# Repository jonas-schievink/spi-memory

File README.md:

# `spi-memory`

This crate provides a generic [`embedded-hal`]-based driver for different
families of SPI Flash and EEPROM chips.

Right now, only 25-series Flash chips are supported. Feel free to send PRs to
support other families though!

Please refer to the [changelog](CHANGELOG.md) to see what changed in the last
releases.

[`embedded-hal`]: https://github.com/rust-embedded/embedded-hal

## Usage

Add an entry to your `Cargo.toml`:

```toml
[dependencies]
spi-memory = "0.2.0"
```

Check the [API Documentation](https://docs.rs/spi-memory/) for how to use the
crate's functionality.

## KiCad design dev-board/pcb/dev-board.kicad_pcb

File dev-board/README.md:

# Development / Testing Board

This directory contains design files and software for a development and testing
PCB that can hold up to 16 SPI memory chips using the 25-series pinout.

The PCB features a micro USB receptacle connected to a USB-to-SPI converter, and
can also be mounted on a Raspberry Pi, directly using the Pi's native SPI
peripheral (and Linux driver). The USB feature is useful for development of the
library on a regular PC, while the latter is useful for performing automated
Hardware-in-the-Loop testing.

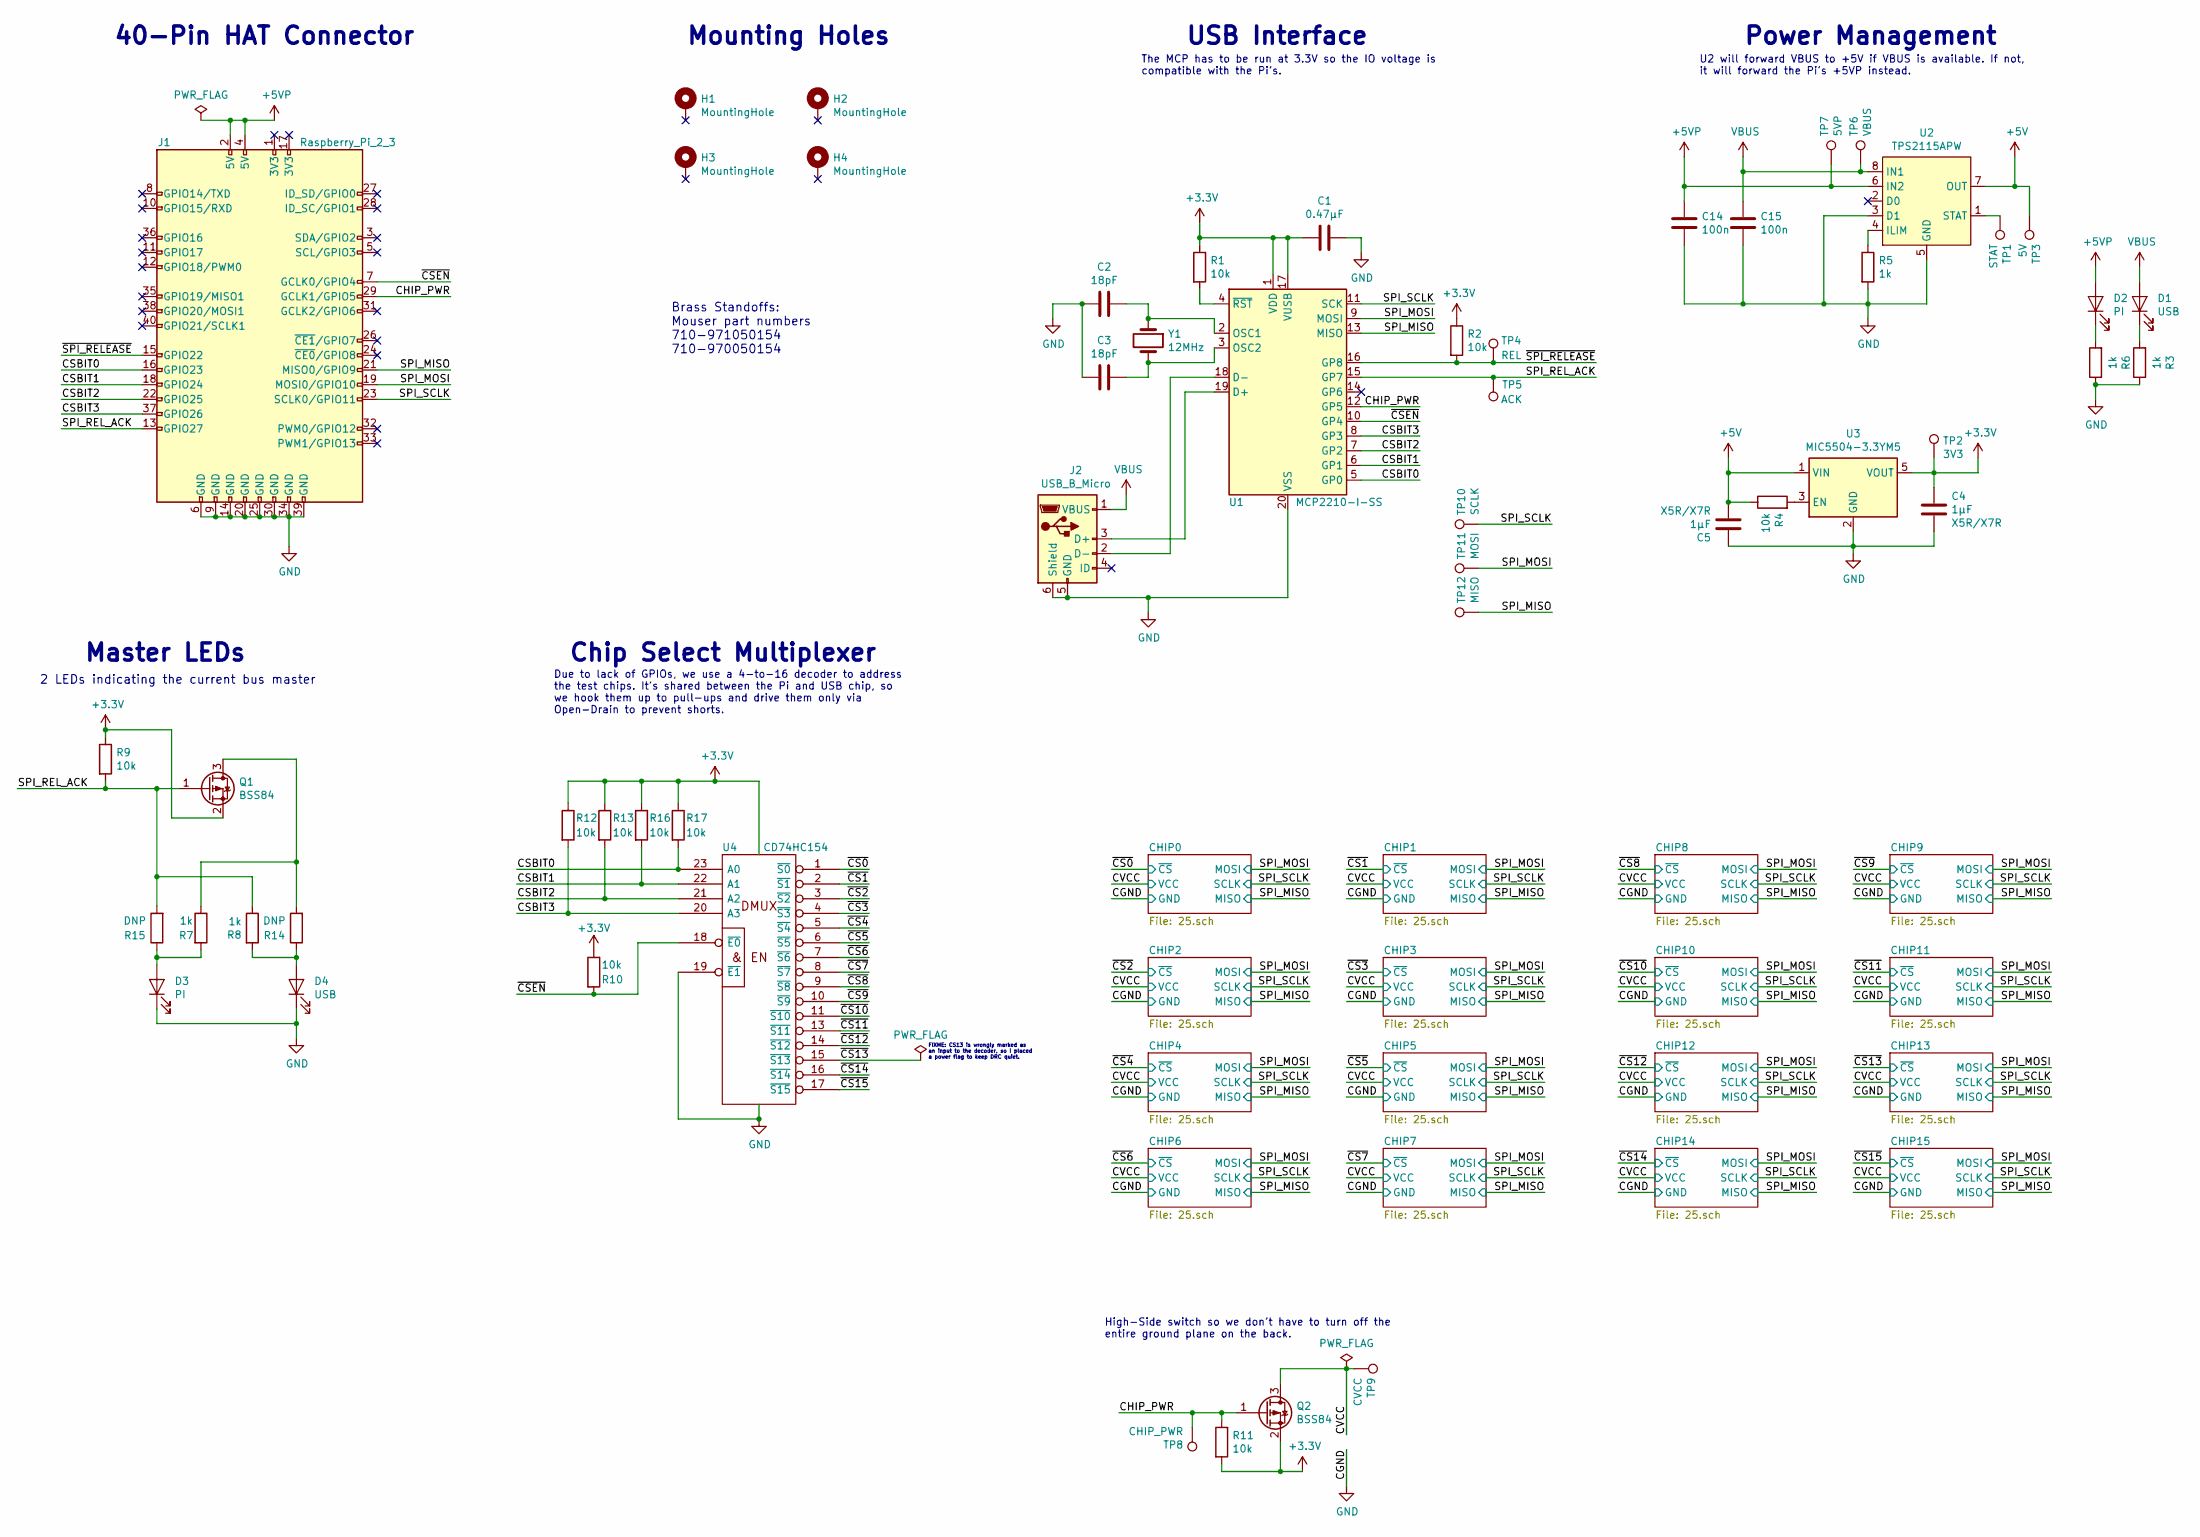
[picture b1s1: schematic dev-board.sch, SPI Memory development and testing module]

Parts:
C1: 0.47µF; C_0805_2012Metric_Pad1.15x1.40mm_HandSolder
C2, C3: 18pF; C_0805_2012Metric_Pad1.15x1.40mm_HandSolder
C4, C5: 1µF; C_0805_2012Metric_Pad1.15x1.40mm_HandSolder
C14, C15: 100n; C_0805_2012Metric_Pad1.15x1.40mm_HandSolder
D1, D4: USB; LED_0805_2012Metric_Pad1.15x1.40mm_HandSolder
D2, D3: PI; LED_0805_2012Metric_Pad1.15x1.40mm_HandSolder
H1, H2, H3, H4: MountingHole; MountingHole_2.7mm_M2.5_Pad
J1: Raspberry_Pi_2_3; PinSocket_2x20_P2.54mm_Vertical
J2: USB_B_Micro; USB_Micro-B_Molex-105017-0001
Q1, Q2: BSS84; SOT-23
R1, R2, R4, R9, R10, R11, R12, R13, R16, R17: 10k; C_0805_2012Metric_Pad1.15x1.40mm_HandSolder
R3, R5, R6, R7, R8: 1k; C_0805_2012Metric_Pad1.15x1.40mm_HandSolder
R14, R15: DNP; C_0805_2012Metric_Pad1.15x1.40mm_HandSolder
TP1: STAT; TestPoint_Pad_D1.5mm
TP2: 3V3; TestPoint_Pad_D1.5mm
TP3: 5V; TestPoint_Pad_D1.5mm
TP4: REL; TestPoint_Pad_D1.5mm
TP5: ACK; TestPoint_Pad_D1.5mm
TP6: VBUS; TestPoint_Pad_D1.5mm
TP7: 5VP; TestPoint_Pad_D1.5mm
TP8: CHIP_PWR; TestPoint_Pad_D1.5mm
TP9: CVCC; TestPoint_Pad_D1.5mm
TP10: SCLK; TestPoint_Pad_D1.5mm
TP11: MOSI; TestPoint_Pad_D1.5mm
TP12: MISO; TestPoint_Pad_D1.5mm
U1: MCP2210-I-SS; SSOP-20_5.3x7.2mm_P0.65mm
U2: TPS2115APW; TSSOP-8_4.4x3mm_P0.65mm
U3: MIC5504-3.3YM5; SOT-23-5
U4: CD74HC154; SOIC-24W_7.5x15.4mm_P1.27mm
Y1: 12MHz; Crystal_SMD_TXC_7A-2Pin_5x3.2mm

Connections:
+3V3: C1.2, C4.1, Q1.2 (S), Q2.2 (S), R1.1, R2.1, R9.1, R10.1, R11.2, R12.1, R13.1, R16.1, R17.1, TP2.1, U1.1 (VDD), U1.17 (VUSB), U3.5 (VOUT), U4.24 (VCC)
+5V: C5.2, R4.1, TP3.1, U2.7 (OUT), U3.1 (VIN)
+5VP: C14.1, D2.2 (A), J1.2 (5V), J1.4 (5V), TP7.1, U2.6 (IN2)
/CHIP_PWR: J1.29 (GCLK1/GPIO5), Q2.1 (G), R11.1, TP8.1, U1.12 (GP5)
/CSBIT0: J1.16 (GPIO23), R17.2, U1.5 (GP0), U4.23 (A0)
/CSBIT1: J1.18 (GPIO24), R16.2, U1.6 (GP1), U4.22 (A1)
/CSBIT2: J1.22 (GPIO25), R13.2, U1.7 (GP2), U4.21 (A2)
/CSBIT3: J1.37 (GPIO26), R12.2, U1.8 (GP3), U4.20 (A3)
/CVCC: Q2.3 (D), TP9.1; also elsewhere on the board
/SPI_MISO: J1.21 (MISO0/GPIO9), TP12.1, U1.13 (MISO); also elsewhere on the board
/SPI_MOSI: J1.19 (MOSI0/GPIO10), TP11.1, U1.9 (MOSI); also elsewhere on the board
/SPI_REL_ACK: J1.13 (GPIO27), Q1.1 (G), R8.1, R9.2, R15.2, TP5.1, U1.15 (GP7)
/SPI_SCLK: J1.23 (SCLK0/GPIO11), TP10.1, U1.11 (SCK); also elsewhere on the board
/~CS0: U4.1 (~S0); also elsewhere on the board
/~CS1: U4.2 (~S1); also elsewhere on the board
/~CS2: U4.3 (~S2); also elsewhere on the board
/~CS3: U4.4 (~S3); also elsewhere on the board
/~CS4: U4.5 (~S4); also elsewhere on the board
/~CS5: U4.6 (~S5); also elsewhere on the board
/~CS6: U4.7 (~S6); also elsewhere on the board
/~CS7: U4.8 (~S7); also elsewhere on the board
/~CS8: U4.9 (~S8); also elsewhere on the board
/~CS9: U4.10 (~S9); also elsewhere on the board
/~CS10: U4.11 (~S10); also elsewhere on the board
/~CS11: U4.13 (~S11); also elsewhere on the board
/~CS12: U4.14 (~S12); also elsewhere on the board
/~CS13: U4.15 (~S13); also elsewhere on the board
/~CS14: U4.16 (~S14); also elsewhere on the board
/~CS15: U4.17 (~S15); also elsewhere on the board
/~CSEN: J1.7 (GCLK0/GPIO4), R10.2, U1.10 (GP4), U4.18 (~E0)
/~SPI_RELEASE: J1.15 (GPIO22), R2.2, TP4.1, U1.16 (GP8)
GND: C1.1, C2.2, C3.2, C4.2, C5.1, C14.2, C15.2, D3.1 (K), D4.1 (K), J1.6 (GND), J1.9 (GND), J1.14 (GND), J1.20 (GND), J1.25 (GND), J1.30 (GND), J1.34 (GND), J1.39 (GND), J2.5 (GND), J2.6 (Shield), R3.1, R5.2, R6.1, U1.20 (VSS), U2.3 (D1), U2.5 (GND), U3.2 (GND), U4.12 (GND), U4.19 (~E1); also elsewhere on the board
unnamed: C2.1, U1.2 (OSC1), Y1.1
unnamed: C3.1, U1.3 (OSC2), Y1.2
unnamed: D1.1 (K), R3.2
unnamed: D2.1 (K), R6.2
unnamed: D3.2 (A), R7.2, R15.1
unnamed: D4.2 (A), R8.2, R14.1
unnamed: J2.2 (D-), U1.18 (D-)
unnamed: J2.3 (D+), U1.19 (D+)
unnamed: Q1.3 (D), R7.1, R14.2
unnamed: R1.2, U1.4 (~RST)
unnamed: R4.2, U3.3 (EN)
unnamed: R5.1, U2.4 (ILIM)
unnamed: TP1.1, U2.1 (STAT)
VBUS: C15.1, D1.2 (A), J2.1 (VBUS), TP6.1, U2.8 (IN1)

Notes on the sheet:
Mounting Holes
40-Pin HAT Connector
USB Interface
Power Management
U2 will forward VBUS to +5V if VBUS is available. If not, it will forward the Pi's +5VP instead.
The MCP has to be run at 3.3V so the IO voltage is compatible with the Pi's.
Brass Standoffs: Mouser part numbers 710-971050154 710-970050154
Master LEDs
2 LEDs indicating the current bus master
Chip Select Multiplexer
Due to lack of GPIOs, we use a 4-to-16 decoder to address the test chips. It's shared between the Pi and USB chip, so we hook them up to pull-ups and drive them only via Open-Drain to prevent shorts.
High-Side switch so we don't have to turn off the entire ground plane on the back.
FIXME: CS13 is wrongly marked as an input to the decoder, so I placed a power flag to keep DRC quiet.

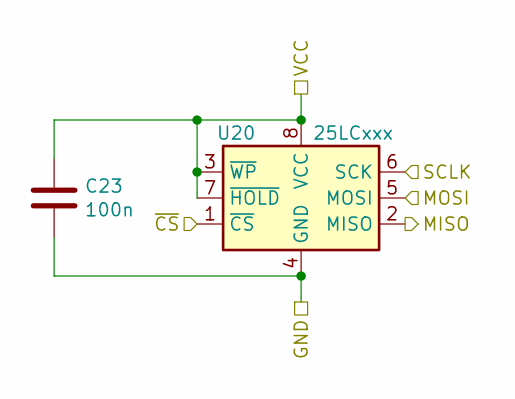
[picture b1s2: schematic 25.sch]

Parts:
C7: 100n; C_0805_2012Metric_Pad1.15x1.40mm_HandSolder
U5: 25LCxxx; SOIC-8_3.9x4.9mm_P1.27mm

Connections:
/CVCC: C7.1, U5.3 (~WP), U5.7 (~HOLD), U5.8 (VCC); also elsewhere on the board
/SPI_MISO: U5.2 (MISO); also elsewhere on the board
/SPI_MOSI: U5.5 (MOSI); also elsewhere on the board
/SPI_SCLK: U5.6 (SCK); also elsewhere on the board
/~CS0: U5.1 (~CS); also elsewhere on the board
GND: C7.2, U5.4 (GND); also elsewhere on the board

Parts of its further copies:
C6, C8, C9, C10, C11, C12, C13, C16, C17, C18, C19, C20, C21, C22, C23: 100n; C_0805_2012Metric_Pad1.15x1.40mm_HandSolder
U6, U7, U8, U9, U10, U11, U12, U13, U14, U15, U16, U17, U18, U19, U20: 25LCxxx; SOIC-8_3.9x4.9mm_P1.27mm

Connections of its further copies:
/CVCC: C6.1, C8.1, C9.1, C10.1, C11.1, C12.1, C13.1, C16.1, C17.1, C18.1, C19.1, C20.1, C21.1, C22.1, C23.1, U6.3 (~WP), U6.7 (~HOLD), U6.8 (VCC), U7.3 (~WP), U7.7 (~HOLD), U7.8 (VCC), U8.3 (~WP), U8.7 (~HOLD), U8.8 (VCC), U9.3 (~WP), U9.7 (~HOLD), U9.8 (VCC), U10.3 (~WP), U10.7 (~HOLD), U10.8 (VCC), U11.3 (~WP), U11.7 (~HOLD), U11.8 (VCC), U12.3 (~WP), U12.7 (~HOLD), U12.8 (VCC), U13.3 (~WP), U13.7 (~HOLD), U13.8 (VCC), U14.3 (~WP), U14.7 (~HOLD), U14.8 (VCC), U15.3 (~WP), U15.7 (~HOLD), U15.8 (VCC), U16.3 (~WP), U16.7 (~HOLD), U16.8 (VCC), U17.3 (~WP), U17.7 (~HOLD), U17.8 (VCC), U18.3 (~WP), U18.7 (~HOLD), U18.8 (VCC), U19.3 (~WP), U19.7 (~HOLD), U19.8 (VCC), U20.3 (~WP), U20.7 (~HOLD), U20.8 (VCC); also elsewhere on the board
/SPI_MISO: U6.2 (MISO), U7.2 (MISO), U8.2 (MISO), U9.2 (MISO), U10.2 (MISO), U11.2 (MISO), U12.2 (MISO), U13.2 (MISO), U14.2 (MISO), U15.2 (MISO), U16.2 (MISO), U17.2 (MISO), U18.2 (MISO), U19.2 (MISO), U20.2 (MISO); also elsewhere on the board
/SPI_MOSI: U6.5 (MOSI), U7.5 (MOSI), U8.5 (MOSI), U9.5 (MOSI), U10.5 (MOSI), U11.5 (MOSI), U12.5 (MOSI), U13.5 (MOSI), U14.5 (MOSI), U15.5 (MOSI), U16.5 (MOSI), U17.5 (MOSI), U18.5 (MOSI), U19.5 (MOSI), U20.5 (MOSI); also elsewhere on the board
/SPI_SCLK: U6.6 (SCK), U7.6 (SCK), U8.6 (SCK), U9.6 (SCK), U10.6 (SCK), U11.6 (SCK), U12.6 (SCK), U13.6 (SCK), U14.6 (SCK), U15.6 (SCK), U16.6 (SCK), U17.6 (SCK), U18.6 (SCK), U19.6 (SCK), U20.6 (SCK); also elsewhere on the board
/~CS1: U6.1 (~CS); also elsewhere on the board
/~CS2: U7.1 (~CS); also elsewhere on the board
/~CS3: U8.1 (~CS); also elsewhere on the board
/~CS4: U9.1 (~CS); also elsewhere on the board
/~CS5: U10.1 (~CS); also elsewhere on the board
/~CS6: U11.1 (~CS); also elsewhere on the board
/~CS7: U12.1 (~CS); also elsewhere on the board
/~CS8: U20.1 (~CS); also elsewhere on the board
/~CS9: U19.1 (~CS); also elsewhere on the board
/~CS10: U18.1 (~CS); also elsewhere on the board
/~CS11: U17.1 (~CS); also elsewhere on the board
/~CS12: U16.1 (~CS); also elsewhere on the board
/~CS13: U15.1 (~CS); also elsewhere on the board
/~CS14: U14.1 (~CS); also elsewhere on the board
/~CS15: U13.1 (~CS); also elsewhere on the board
GND: C6.2, C8.2, C9.2, C10.2, C11.2, C12.2, C13.2, C16.2, C17.2, C18.2, C19.2, C20.2, C21.2, C22.2, C23.2, U6.4 (GND), U7.4 (GND), U8.4 (GND), U9.4 (GND), U10.4 (GND), U11.4 (GND), U12.4 (GND), U13.4 (GND), U14.4 (GND), U15.4 (GND), U16.4 (GND), U17.4 (GND), U18.4 (GND), U19.4 (GND), U20.4 (GND); also elsewhere on the board

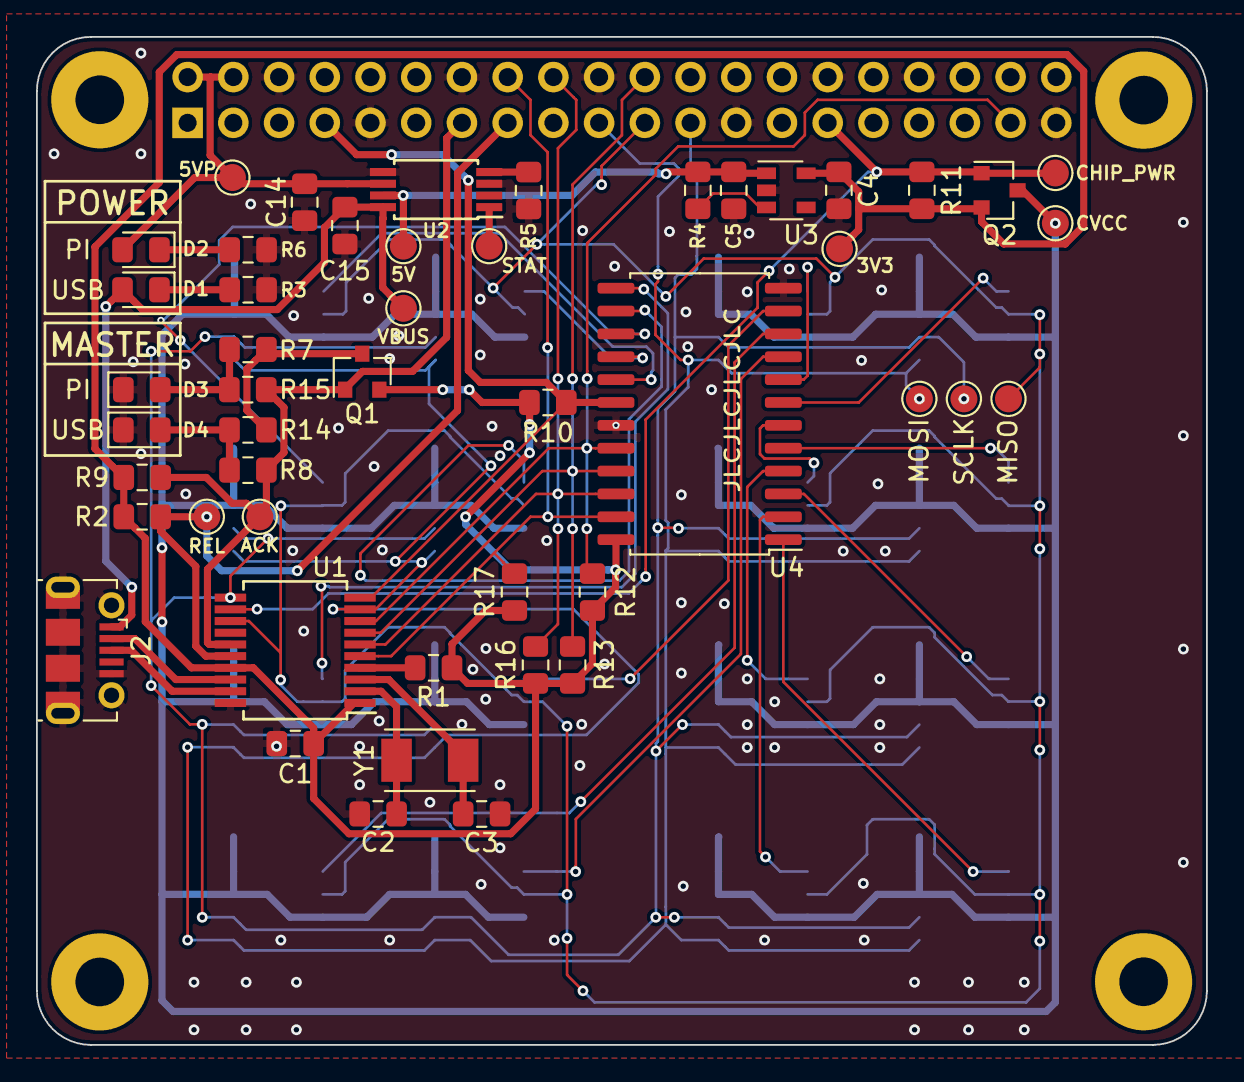
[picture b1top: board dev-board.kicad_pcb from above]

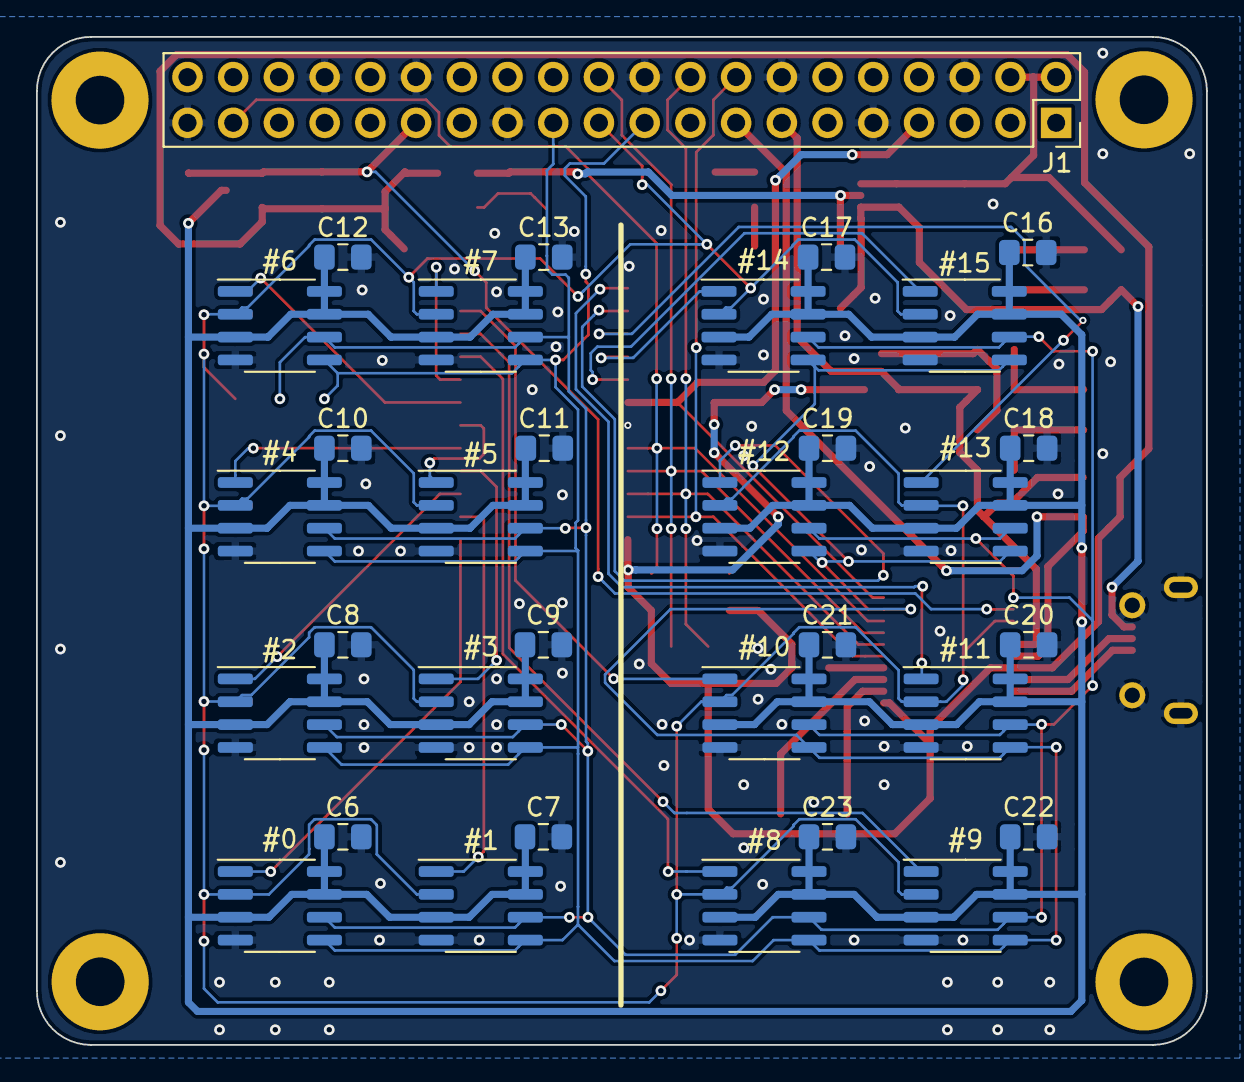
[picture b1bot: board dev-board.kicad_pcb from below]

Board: 2 copper layers, 65.0 x 56.0 mm, 85 parts (33 on the bottom side), 46 nets.

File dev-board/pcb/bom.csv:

Reference, Quantity, Value, Footprint, Datasheet, Comment, ECS Part no
C1 ,1,0.47µF,Capacitor_SMD:C_0805_2012Metric_Pad1.15x1.40mm_HandSolder,~,0.22-0.47µF according to MCP DS,
C15 C14 C6 C7 C8 C9 C10 C11 C12 C13 C16 C17 C18 C19 C20 C21 C22 C23 ,18,100n,Capacitor_SMD:C_0805_2012Metric_Pad1.15x1.40mm_HandSolder,~,,
C2 C3 ,2,18pF,Capacitor_SMD:C_0805_2012Metric_Pad1.15x1.40mm_HandSolder,~,,
C4 C5 ,2,1µF,Capacitor_SMD:C_0805_2012Metric_Pad1.15x1.40mm_HandSolder,~,X5R/X7R,
D1 D4 ,2,USB,LED_SMD:LED_0805_2012Metric_Pad1.15x1.40mm_HandSolder,~,,
D2 D3 ,2,PI,LED_SMD:LED_0805_2012Metric_Pad1.15x1.40mm_HandSolder,~,,
H1 H2 H3 H4 ,4,MountingHole,MountingHole:MountingHole_2.7mm_M2.5_Pad,~,,
J1 ,1,Raspberry_Pi_2_3,Connector_PinSocket_2.54mm:PinSocket_2x20_P2.54mm_Vertical,https://www.raspberrypi.org/documentation/hardware/raspberry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,,
J2 ,1,USB_B_Micro,Connector_USB:USB_Micro-B_Molex-105017-0001,~,,
Q2 Q1 ,2,BSS84,Package_TO_SOT_SMD:SOT-23,http://assets.nexperia.com/documents/data-sheet/BSS84.pdf,,
R1 R2 R4 R9 R10 R11 ,6,10k,Capacitor_SMD:C_0805_2012Metric_Pad1.15x1.40mm_HandSolder,~,1-10K according to MCP DS,
R15 R14 ,2,DNP,Capacitor_SMD:C_0805_2012Metric_Pad1.15x1.40mm_HandSolder,~,,
R5 R3 R6 R7 R8 ,5,1k,Capacitor_SMD:C_0805_2012Metric_Pad1.15x1.40mm_HandSolder,~,Ilim is 500/Rlim,
RN1 ,1,10k,Resistor_SMD:R_Array_Convex_4x0603,~,,
TP1 ,1,STAT,TestPoint:TestPoint_Pad_D1.5mm,~,,
TP10 ,1,SCLK,TestPoint:TestPoint_Pad_D1.5mm,~,,
TP11 ,1,MOSI,TestPoint:TestPoint_Pad_D1.5mm,~,,
TP12 ,1,MISO,TestPoint:TestPoint_Pad_D1.5mm,~,,
TP2 ,1,3V3,TestPoint:TestPoint_Pad_D1.5mm,~,,
TP3 ,1,5V,TestPoint:TestPoint_Pad_D1.5mm,~,,
TP4 ,1,REL,TestPoint:TestPoint_Pad_D1.5mm,~,,
TP5 ,1,ACK,TestPoint:TestPoint_Pad_D1.5mm,~,,
TP6 ,1,VBUS,TestPoint:TestPoint_Pad_D1.5mm,~,,
TP7 ,1,5VP,TestPoint:TestPoint_Pad_D1.5mm,~,,
TP8 ,1,CHIP_PWR,TestPoint:TestPoint_Pad_D1.5mm,~,,
TP9 ,1,CVCC,TestPoint:TestPoint_Pad_D1.5mm,~,,
U1 ,1,MCP2210-I-SS,Package_SO:SSOP-20_5.3x7.2mm_P0.65mm,https://ww1.microchip.com/downloads/en/DeviceDoc/22288A.pdf,,
U2 ,1,TPS2115APW,Package_SO:TSSOP-8_4.4x3mm_P0.65mm,http://www.ti.com/lit/ds/symlink/tps2115a.pdf,,
U3 ,1,MIC5504-3.3YM5,Package_TO_SOT_SMD:SOT-23-5,http://ww1.microchip.com/downloads/en/DeviceDoc/MIC550X.pdf,,
U4 ,1,CD74HC154,Package_SO:SOIC-24W_7.5x15.4mm_P1.27mm,http://www.ti.com/lit/ds/symlink/cd74hc154.pdf,,
U5 U6 U7 U8 U9 U10 U11 U12 U13 U14 U15 U16 U17 U18 U19 U20 ,16,25LCxxx,Package_SO:SOIC-8_3.9x4.9mm_P1.27mm,http://ww1.microchip.com/downloads/en/DeviceDoc/21832H.pdf,,
Y1 ,1,12MHz,Crystal:Crystal_SMD_TXC_7A-2Pin_5x3.2mm,https://www.mouser.de/datasheet/2/122/ecx-53r-17605.pdf,,ECS-120-18-30-JEM-TR

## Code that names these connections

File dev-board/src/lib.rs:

//! Internal support crate for the dev board.

// #0 = W25Q16JVSNIQ 16Mbit 133 MHz Flash

use bitflags::bitflags;
use embedded_hal::blocking::spi;
use embedded_hal::digital::v2::OutputPin;
use log::info;
use mcp2210::*;
use std::fmt::Debug;
use std::ops::DerefMut;
use std::sync::{Arc, Mutex};
use std::thread;
use std::time::Duration;

type Error = Box<dyn std::error::Error>;
type Result<T> = std::result::Result<T, Error>;

/// A connection to a dev board.
pub trait DevBoard
where
    <Self::ChipSelect as OutputPin>::Error: Debug,
{
    type ChipSelect: OutputPin;
    type Spi: spi::Transfer<u8>;

    /// Controls `CVCC`.
    fn set_chip_power(&mut self, on: bool) -> Result<()>;

    /// Sets the SPI transfer frequency.
    ///
    /// The MCP2210 has a max. frequency of 12 MHz.
    fn set_freq(&mut self, hz: u32) -> Result<()>;

    /// Obtains access to the a test chip.
    ///
    /// # Parameters
    ///
    /// * `chip`: The chip number as shows on the back of the PCB. 0-15.
    ///
    /// # Panics
    ///
    /// This function will panic when `chip` is not in range 0-15.
    fn access(&mut self, chip: u8) -> (Self::Spi, Self::ChipSelect);
}

/// Opens a dev board connected via USB.
pub fn open_usb() -> Result<UsbConnection> {
    let devices = mcp2210::scan_devices()?;
    match devices.len() {
        0 => {
            return Err("No MCP2210 device found (are the access permissions correct?)".into());
        }
        1 => {
            let mcp = Mcp2210::open(&devices[0])?;
            info!("successfully opened '{}'", devices[0].display());

            // Reset the chips
            let mut board = UsbConnection {
                mcp: McpRef {
                    mcp: Arc::new(Mutex::new(mcp)),
                },
            };

            // Make sure that the MCP is configured correctly.
            {
                let mut mcp = board.mcp();
                verify_mcp_nvram(&mut mcp)?;
            }

            board.set_chip_power(false)?;
            thread::sleep(Duration::from_millis(10));
            board.set_chip_power(true)?;
            Ok(board)
        }
        n => {
            let paths = devices
                .iter()
                .map(|path| path.display().to_string())
                .collect::<Vec<_>>()
                .join(", ");

            return Err(format!(
                "Found {} MCP2210 devices. Please remove all but one. ({})",
                n, paths
            )
            .into());
        }
    }
}

pub const SAFE_CHIP_SETTINGS: ChipSettings = ChipSettings {
    // CSBIT0-3 are GPIOs
    gp0_mode: PinMode::Gpio,
    gp1_mode: PinMode::Gpio,
    gp2_mode: PinMode::Gpio,
    gp3_mode: PinMode::Gpio,
    // \CSEN
    gp4_mode: PinMode::Gpio,
    // CHIP_PWR
    gp5_mode: PinMode::Gpio,
    gp6_mode: PinMode::Gpio,
    // SPI_REL_ACK
    gp7_mode: PinMode::Dedicated,
    // \SPI_RELEASE
    gp8_mode: PinMode::Dedicated,
    default_gpio_value: GpioValue::ALL_LOW,
    default_gpio_direction: GpioDirection::ALL_INPUTS,
    remote_wakeup: false,
    interrupt_mode: InterruptMode::None,
    bus_release: true,
    nvram_access_control: NvramAccessControl::None,
};

pub fn verify_mcp_nvram(mcp: &mut Mcp2210) -> Result<()> {
    let chip_settings = mcp.get_nvram_chip_settings()?;
    if chip_settings != SAFE_CHIP_SETTINGS {
        return Err(format!(
            "NVRAM chip settings were not set correctly. Expected: {:?}; Got: {:?}",
            SAFE_CHIP_SETTINGS, chip_settings
        )
        .into());
    }

    let chip_settings = mcp.get_chip_settings()?;
    if chip_settings != SAFE_CHIP_SETTINGS {
        return Err(format!(
            "Active chip settings were not set to NVRAM settings. Expected: {:?}; Got: {:?}",
            SAFE_CHIP_SETTINGS, chip_settings
        )
        .into());
    }

    Ok(())
}

#[derive(Clone)]
pub struct McpRef {
    mcp: Arc<Mutex<Mcp2210>>,
}

bitflags! {
    struct Gpios: u16 {
        const CSBIT0 = (1 << 0);
        const CSBIT1 = (1 << 1);
        const CSBIT2 = (1 << 2);
        const CSBIT3 = (1 << 3);
        const N_CSEN = (1 << 4);
        const N_CHIP_PWR = (1 << 5);
    }
}

impl McpRef {
    fn get_gpios(&self) -> Result<Gpios> {
        let mut mcp = self.mcp();
        let dir = mcp.get_gpio_direction()?;
        Ok(Gpios::from_bits_truncate(dir.bits()))
    }

    /// Sets the open-drain GPIO values.
    fn set_gpios(&mut self, gpios: Gpios) -> Result<()> {
        // Direction bits: 1 == input, 0 == output
        // Value bits are all-0
        let dir = GpioDirection::from_bits(gpios.bits()).unwrap();

        let mut mcp = self.mcp();
        mcp.set_gpio_direction(dir)?;
        Ok(())
    }

    fn mcp(&self) -> impl DerefMut<Target = Mcp2210> + '_ {
        self.mcp.lock().unwrap_or_else(|err| err.into_inner())
    }
}

pub struct UsbConnection {
    mcp: McpRef,
}

impl UsbConnection {
    fn mcp(&self) -> impl DerefMut<Target = Mcp2210> + '_ {
        self.mcp.mcp()
    }
}

impl DevBoard for UsbConnection {
    type ChipSelect = UsbChipSelect;
    type Spi = UsbSpi;

    fn set_chip_power(&mut self, on: bool) -> Result<()> {
        let gpios = self.mcp.get_gpios()?;
        if on {
            self.mcp.set_gpios(gpios & !Gpios::N_CHIP_PWR);
        } else {
            self.mcp.set_gpios(gpios | Gpios::N_CHIP_PWR);
        }

        Ok(())
    }

    fn set_freq(&mut self, hz: u32) -> Result<()> {
        let mut mcp = self.mcp();
        let mut settings = mcp.get_spi_transfer_settings()?;
        settings.bit_rate = hz;
        mcp.set_spi_transfer_settings(&settings)?;
        Ok(())
    }

    fn access(&mut self, chip: u8) -> (Self::Spi, Self::ChipSelect) {
        assert!(chip < 16);

        let spi = UsbSpi {
            mcp: self.mcp.clone(),
        };
        let cs = UsbChipSelect {
            mcp: self.mcp.clone(),
            cs: chip,
        };

        (spi, cs)
    }
}

pub struct UsbChipSelect {
    mcp: McpRef,
    /// Chip select pin number (0-15).
    cs: u8,
}

impl OutputPin for UsbChipSelect {
    type Error = Error;

    /// Assert the chip select line, pulling it low and pulling all other CS lines high.
    fn set_low(&mut self) -> Result<()> {
        let mut gpios = self.mcp.get_gpios()?;

        let cs = Gpios::from_bits(u16::from(self.cs & 0b1111)).unwrap();
        let csmask = Gpios::from_bits(0b1111).unwrap();

        gpios &= !csmask;
        gpios |= cs;
        gpios &= !Gpios::N_CSEN; // Pull \CSEN low

        self.mcp.set_gpios(gpios)?;
        Ok(())
    }

    /// Deassert the chip select line.
    fn set_high(&mut self) -> Result<()> {
        let mut gpios = self.mcp.get_gpios()?;
        gpios |= Gpios::N_CSEN;
        self.mcp.set_gpios(gpios)?;
        Ok(())
    }
}

/// MCP2210 wrapper that implements the embedded-hal SPI trait.
pub struct UsbSpi {
    mcp: McpRef,
}

impl spi::Transfer<u8> for UsbSpi {
    type Error = Error;

    fn transfer<'w>(&mut self, words: &'w mut [u8]) -> Result<&'w [u8]> {
        let mut buf = Vec::with_capacity(words.len());
        let mut mcp = self.mcp.mcp();
        mcp.spi_transfer_to_end(words, &mut buf)?;

        assert_eq!(buf.len(), words.len());
        words.copy_from_slice(&buf);
        Ok(words)
    }
}

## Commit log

2019-05-24 Fix Travis
2019-05-24 Release 0.1.0
2019-05-31 Fix typo
2019-08-18 adding the FlashWrite, EepromWrite and Read traits
2019-08-19 reworking the new traits
2019-08-20 adding erase_all and write_bytes implementations
2019-08-21 finalizing the trait impl on series25 chips, adding a prelude file which exports the BlockDevice and Read trait and formatting the crate with cargo fmt
2019-08-21 addressing review points
2019-08-21 Update comment on erase times
2019-08-22 more review points addressed
2019-08-22 commented the wrong addr
2019-08-22 Nit 1
2019-08-22 Nit 2
2019-08-22 Adding traits for read, write and erase functions (#5)
    * adding the FlashWrite, EepromWrite and Read traits
    * reworking the new traits
    * adding erase_all and write_bytes implementations
    * finalizing the trait impl on series25 chips, adding a prelude file which exports the BlockDevice and Read trait and formatting the crate with cargo fmt
    * finalizing the trait impl on series25 chips, adding a prelude file which exports the BlockDevice and Read trait and formatting the crate with cargo fmt
    * addressing review points
2019-08-25 adding an (undocumented) implementation of the w25m concept
2019-08-25 adding BlockDevice and Read impls for w25m
2019-08-31 read, write and reset working roughly for w25n, more testing to be done to verify
2019-09-22 Check in BOM and gerbers
2019-09-22 Initial dev board PCB design
2019-09-22 Use "10k" resistor value consistently
    Otherwise the BOM creates an extra group that isn't needed.
2019-09-29 working API for the w25n series, everything tested
2019-10-03 adding support for spi stack chips
2019-10-06 increasing code reusage by only having one central spi_command function
2019-10-06 formatting and a bit of docs
2019-10-11 Include footprint values in gerbers
    Fixes #11
2019-10-15 Replace RN1 with 4 0804 resistors
    Closes #9
2019-10-19 More work on the bringup tool
2019-10-20 Add a dev-board support crate
    MCP2210 is still a bit buggy, but I was able to read the JEDEC ID from
    the chip.
2019-10-21 Update stm32f4xx-hal requirement from 0.5.0 to 0.6.0
    Updates the requirements on [stm32f4xx-hal](https://github.com/stm32-rs/stm32f4xx-hal) to permit the latest version.
    - [Release notes](https://github.com/stm32-rs/stm32f4xx-hal/releases)
    - [Changelog](https://github.com/stm32-rs/stm32f4xx-hal/blob/master/CHANGELOG.md)
    - [Commits](https://github.com/stm32-rs/stm32f4xx-hal/compare/v0.5.0...v0.6.0)
2020-03-09 Update stm32f4xx-hal requirement from 0.5.0 to 0.7.0
    Updates the requirements on [stm32f4xx-hal](https://github.com/stm32-rs/stm32f4xx-hal) to permit the latest version.
    - [Release notes](https://github.com/stm32-rs/stm32f4xx-hal/releases)
    - [Changelog](https://github.com/stm32-rs/stm32f4xx-hal/blob/master/CHANGELOG.md)
    - [Commits](https://github.com/stm32-rs/stm32f4xx-hal/compare/v0.5.0...v0.7.0)
2020-03-25 Support more thorough device identification
    - Count continuation bytes when decoding the JEDEC identifier
    - Make the manufacturer code available for verification.
    - Export the count of continuations that prefix the Identifier
    - Move jedec ID parsing into Identification, draft test
    - Export manufacturer-specific device_id
2020-03-25 Remove default target from Cargo config
2020-03-25 Make the lib testable
2020-03-25 Run unit tests in CI
2020-03-25 Update stm32f4xx-hal requirement from 0.5.0 to 0.7.0 (#15)
    Updates the requirements on [stm32f4xx-hal](https://github.com/stm32-rs/stm32f4xx-hal) to permit the latest version.
    - [Release notes](https://github.com/stm32-rs/stm32f4xx-hal/releases)
    - [Changelog](https://github.com/stm32-rs/stm32f4xx-hal/blob/master/CHANGELOG.md)
    - [Commits](https://github.com/stm32-rs/stm32f4xx-hal/compare/v0.5.0...v0.7.0)
2020-03-25 Reorder methods to improve docs
2020-03-25 Clean up docs a little
2020-03-25 Release 0.2.0
2020-04-18 Add changelog for 0.2
2020-04-18 Fix features listed in crate-level comment
2020-04-18 Move `Error` into its own module
2020-04-18 Implement `Display` for `Error`
    Closes #12
2020-04-18 Fix changelog and add entry
2020-04-30 Update stm32f4xx-hal requirement from 0.7.0 to 0.8.0
    Updates the requirements on [stm32f4xx-hal](https://github.com/stm32-rs/stm32f4xx-hal) to permit the latest version.
    - [Release notes](https://github.com/stm32-rs/stm32f4xx-hal/releases)
    - [Changelog](https://github.com/stm32-rs/stm32f4xx-hal/blob/master/CHANGELOG.md)
    - [Commits](https://github.com/stm32-rs/stm32f4xx-hal/compare/v0.7.0...v0.8.0)
2020-05-11 Update stm32f4xx-hal requirement from 0.7.0 to 0.8.1
    Updates the requirements on [stm32f4xx-hal](https://github.com/stm32-rs/stm32f4xx-hal) to permit the latest version.
    - [Release notes](https://github.com/stm32-rs/stm32f4xx-hal/releases)
    - [Changelog](https://github.com/stm32-rs/stm32f4xx-hal/blob/master/CHANGELOG.md)
    - [Commits](https://github.com/stm32-rs/stm32f4xx-hal/compare/v0.7.0...v0.8.1)
2020-06-01 Update stm32f4xx-hal requirement from 0.7.0 to 0.8.2
    Updates the requirements on [stm32f4xx-hal](https://github.com/stm32-rs/stm32f4xx-hal) to permit the latest version.
    - [Release notes](https://github.com/stm32-rs/stm32f4xx-hal/releases)
    - [Changelog](https://github.com/stm32-rs/stm32f4xx-hal/blob/master/CHANGELOG.md)
    - [Commits](https://github.com/stm32-rs/stm32f4xx-hal/compare/v0.7.0...v0.8.2)
2020-06-01 Borrow spi instead of owning
2020-06-12 Update stm32f4xx-hal requirement from 0.7.0 to 0.8.3
    Updates the requirements on [stm32f4xx-hal](https://github.com/stm32-rs/stm32f4xx-hal) to permit the latest version.
    - [Release notes](https://github.com/stm32-rs/stm32f4xx-hal/releases)
    - [Changelog](https://github.com/stm32-rs/stm32f4xx-hal/blob/master/CHANGELOG.md)
    - [Commits](https://github.com/stm32-rs/stm32f4xx-hal/compare/v0.7.0...v0.8.3)
2020-06-25 Added a utility for interacting with SPI flash devices
2020-07-15 Add Microchip 25LCxx specific changes
2020-07-15 Compile error on usize vs u16
2020-07-15 ReadDeviceId fix - need 4 dummy bytes
2020-07-15 Fix CI/CD for warnings that become errors
2020-09-10 Moved the driver to type states, needs merging with traits again
2020-10-15 Update cortex-m-semihosting requirement from 0.3.3 to 0.4.0
    Updates the requirements on [cortex-m-semihosting](https://github.com/rust-embedded/cortex-m) to permit the latest version.
    - [Release notes](https://github.com/rust-embedded/cortex-m/releases)
    - [Changelog](https://github.com/rust-embedded/cortex-m/blob/master/CHANGELOG.md)
    - [Commits](https://github.com/rust-embedded/cortex-m/compare/c-m-sh-v0.3.5...v0.4.0)
2020-11-03 Make BlockDevice depend on Write<u8> to remove mutable reference on write buffer
2020-11-11 Update cortex-m requirement from 0.6.0 to 0.7.0
    Updates the requirements on [cortex-m](https://github.com/rust-embedded/cortex-m) to permit the latest version.
    - [Release notes](https://github.com/rust-embedded/cortex-m/releases)
    - [Changelog](https://github.com/rust-embedded/cortex-m/blob/master/CHANGELOG.md)
    - [Commits](https://github.com/rust-embedded/cortex-m/compare/v0.6.0...v0.7.0)
2020-12-01 spi deep sleep
2021-01-26 Update cortex-m requirement from 0.6.0 to 0.7.1
    Updates the requirements on [cortex-m](https://github.com/rust-embedded/cortex-m) to permit the latest version.
    - [Release notes](https://github.com/rust-embedded/cortex-m/releases)
    - [Changelog](https://github.com/rust-embedded/cortex-m/blob/master/CHANGELOG.md)
    - [Commits](https://github.com/rust-embedded/cortex-m/compare/v0.6.0...v0.7.1)
2021-03-08 Update cortex-m requirement from 0.6.0 to 0.7.2
    Updates the requirements on [cortex-m](https://github.com/rust-embedded/cortex-m) to permit the latest version.
    - [Release notes](https://github.com/rust-embedded/cortex-m/releases)
    - [Changelog](https://github.com/rust-embedded/cortex-m/blob/master/CHANGELOG.md)
    - [Commits](https://github.com/rust-embedded/cortex-m/compare/v0.6.0...v0.7.2)
2021-04-05 Update stm32f4xx-hal requirement from 0.7.0 to 0.9.0
    Updates the requirements on [stm32f4xx-hal](https://github.com/stm32-rs/stm32f4xx-hal) to permit the latest version.
    - [Release notes](https://github.com/stm32-rs/stm32f4xx-hal/releases)
    - [Changelog](https://github.com/stm32-rs/stm32f4xx-hal/blob/master/CHANGELOG.md)
    - [Commits](https://github.com/stm32-rs/stm32f4xx-hal/compare/v0.7.0...v0.9.0)
2021-04-29 Upgrade to GitHub-native Dependabot
2021-05-13 Added low power modes
2021-05-13 Fixed bugs in low power modes, and added delay
2021-05-13 More bugs fixed with low power
2022-01-27 Make `command` public to allow usage of custom commands
    Many flash chips implement custom extensions, for example the
    GD25Q16CSIG with a 128 bit unique id or Window 25Q32JVSIQ with a 64 bit
    unique id.
    Without this change applications would need to reconstruct `SPI` after
    dropping `Flash` or only execute custom commands before constructing
    `Flash`, both rather ... unideal solutions.
